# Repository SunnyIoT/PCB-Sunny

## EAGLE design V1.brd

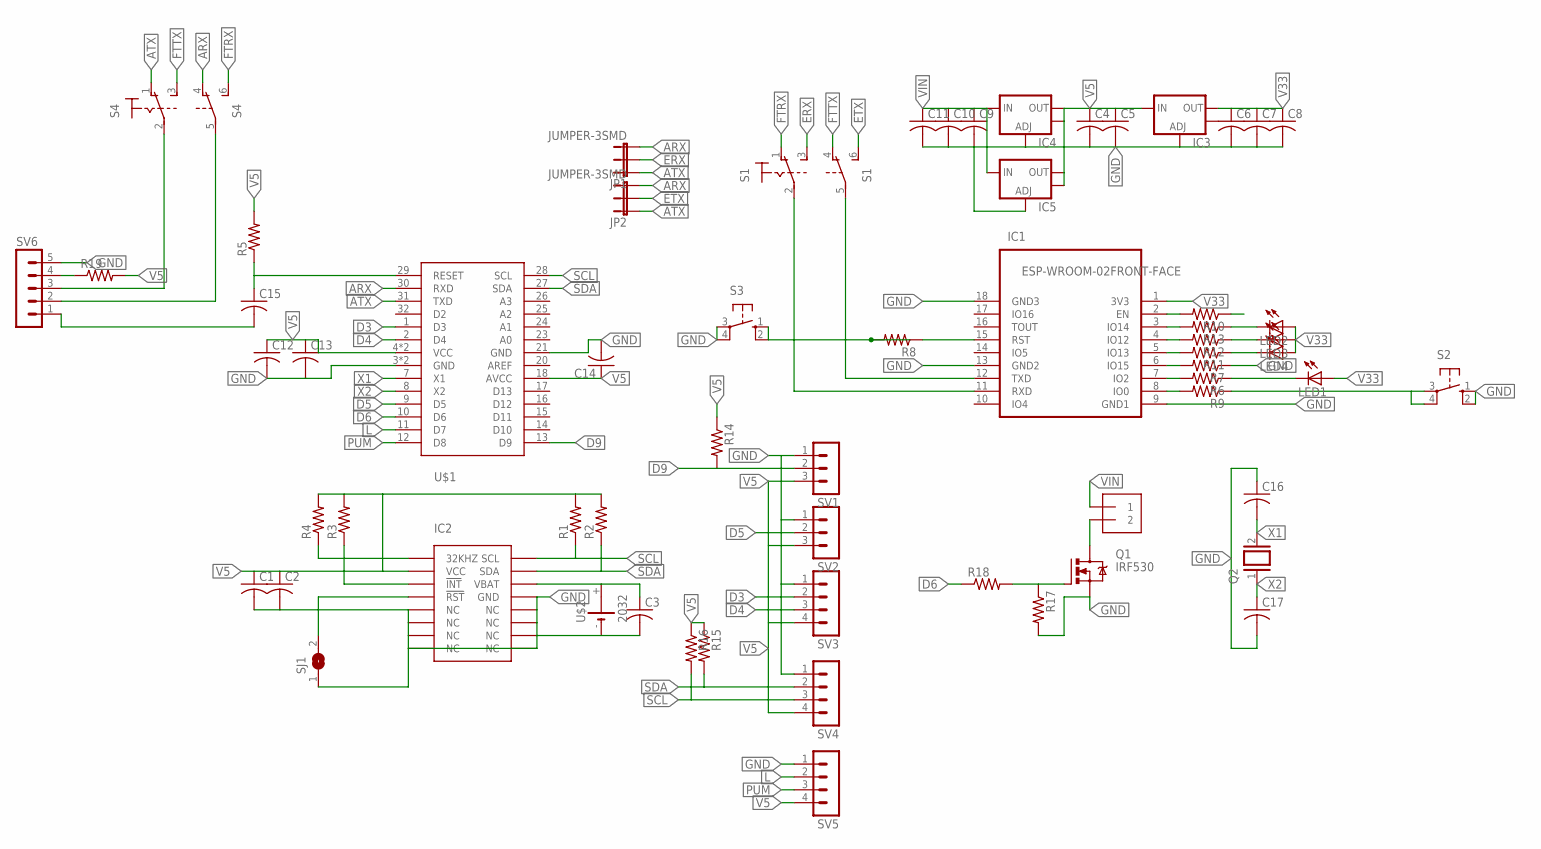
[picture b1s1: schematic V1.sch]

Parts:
C1, C2, C3, C4, C5, C6, C7, C8, C9, C10, C11, C12, C13, C14, C15, C16, C17: C-USC0805; C0805
IC1: ESP-WROOM-02FRONT-FACE; FRONT-FACE
IC2: DS3231SOIC-16W; SOIC-16W
IC3, IC4, IC5: V_REG_LM1117SOT223; SOT223
J1: 1X2-3.5MM; 3.5MMTERM
JP1, JP2: JUMPER-3SMD; SJ_3
LED1, LED2, LED3, LED4: LED5MM
Q1: IRF530; TO220BV
Q2: XTAL/S; QS
R1, R2, R3, R4, R5, R6, R7, R8, R9, R10, R11, R12, R13, R14, R15, R16, R17, R18, R19: R-US_R0805; R0805
S1, S4: 320-938
S2, S3: 10-XX; B3F-10XX
SJ1: SJW
SV1, SV2: MA03-1
SV3, SV4, SV5: MA04-1
SV6: MA05-1
U$1: ATMEGA328P; TQFP32-08
U$2: 2032; KZH20SMD

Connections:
ARX: C15.1, JP1.3, JP2.3, R5.1, S4.4 (O), U$1.29 (RESET), U$1.30 (RXD)
ATX: JP1.1, JP2.1, S4.1 (O), U$1.31 (TXD)
D3: SV3.2, U$1.1 (D3)
D4: SV3.3, U$1.2 (D4)
D5: SV2.2, U$1.9 (D5)
D6: R18.1, U$1.10 (D6)
D9: R14.2, SV1.2, U$1.13 (D9)
ERX: JP1.2, S1.3 (S)
ETX: JP2.2, S1.6 (S)
FTRX: S1.1 (O), S4.6 (S)
FTTX: S1.4 (O), S4.3 (S)
GND: C1.2, C2.2, C3.2, C4.2, C5.2, C6.2, C7.2, C8.2, C9.2, C10.2, C11.2, C12.2, C13.2, C14.2, C16.1, C17.2, IC1.9 (GND1), IC1.13 (GND2), IC1.18 (GND3), IC2.5 (NC), IC2.6 (NC), IC2.7 (NC), IC2.8 (NC), IC2.9 (NC), IC2.10 (NC), IC2.11 (NC), IC2.12 (NC), IC2.13 (GND), IC3.1 (ADJ), IC4.1 (ADJ), IC5.1 (ADJ), Q1.S, R7.1, R17.2, S2.1 (S), S2.2 (S1), S3.3, S3.4 (P1), SJ1.1, SV1.1, SV2.1, SV3.1, SV4.1, SV5.1, SV6.5, U$1.3 (GND), U$1.5 (GND), U$1.21 (GND), U$2.-
L: SV5.2, U$1.11 (D7)
unnamed: IC1.11 (RXD), S1.2
unnamed: C3.1, IC2.14 (VBAT), U$2.+
unnamed: IC1.12 (TXD), S1.5
unnamed: IC1.6 (IO15), R7.2
unnamed: IC2.3 (!INT), R3.1
unnamed: IC2.4 (!RST), SJ1.2
unnamed: IC1.7 (IO2), R6.2
unnamed: IC2.1 (32KHZ), R4.1
unnamed: IC1.8 (IO0), R9.2
unnamed: IC1.15 (RST), R8.1
unnamed: R8.2, S3.1 (S), S3.2 (S1)
unnamed: IC1.3 (IO14), R13.2
unnamed: IC1.4 (IO12), R12.2
unnamed: R9.1, S2.3, S2.4 (P1)
unnamed: IC1.2 (EN), R10.2
unnamed: IC1.5 (IO13), R11.2
unnamed: LED2.K (C), R13.1
unnamed: LED3.K (C), R12.1
unnamed: LED4.K (C), R11.1
unnamed: J1.2, Q1.D
unnamed: Q1.G, R17.1, R18.2
unnamed: C15.2, SV6.1
unnamed: S4.5, SV6.2
unnamed: S4.2, SV6.3
unnamed: R19.1, SV6.4
PUM: SV5.3, U$1.12 (D8)
SCL: IC2.16 (SCL), R1.1, R16.2, SV4.3, U$1.28 (SCL)
SDA: IC2.15 (SDA), R2.1, R15.2, SV4.2, U$1.27 (SDA)
V5: C1.1, C2.1, C4.1, C5.1, C12.1, C13.1, C14.1, IC2.2 (VCC), IC3.3 (IN), IC4.2 (OUT), IC4.4 (OUT), IC5.2 (OUT), IC5.4 (OUT), R1.2, R2.2, R3.2, R4.2, R5.2, R14.1, R15.1, R16.1, R19.2, SV1.3, SV2.3, SV3.4, SV4.4, SV5.4, U$1.4 (VCC), U$1.6 (VCC), U$1.18 (AVCC)
V33: C6.1, C7.1, C8.1, IC1.1 (3V3), IC3.2 (OUT), LED1.A, LED1.K (C), LED2.A, LED3.A, LED4.A, R6.1
VIN: C9.1, C10.1, C11.1, IC4.3 (IN), IC5.3 (IN), J1.1
X1: C16.2, Q2.2, U$1.7 (X1)
X2: C17.1, Q2.1, U$1.8 (X2)

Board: 2 copper layers, 63 parts (1 on the bottom side), 46 nets, no tracks yet.

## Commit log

2016-12-02 no message

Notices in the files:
parts and their libraries:
SparkFun-Passives: Licensing: CC v3.0 Share-Alike You are welcome to use this library for commercial purposes.
